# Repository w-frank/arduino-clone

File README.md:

# Battery Powered Arduino Clone

A simple battery powered Arduino clone including:
* 16 MHz ATmega328P
* I2C 2 Mbit EEPROM (24LC1025)
* I2C real-time clock/calendar (DS1337)
* UART, I2C, SPI and 7 GPIOs

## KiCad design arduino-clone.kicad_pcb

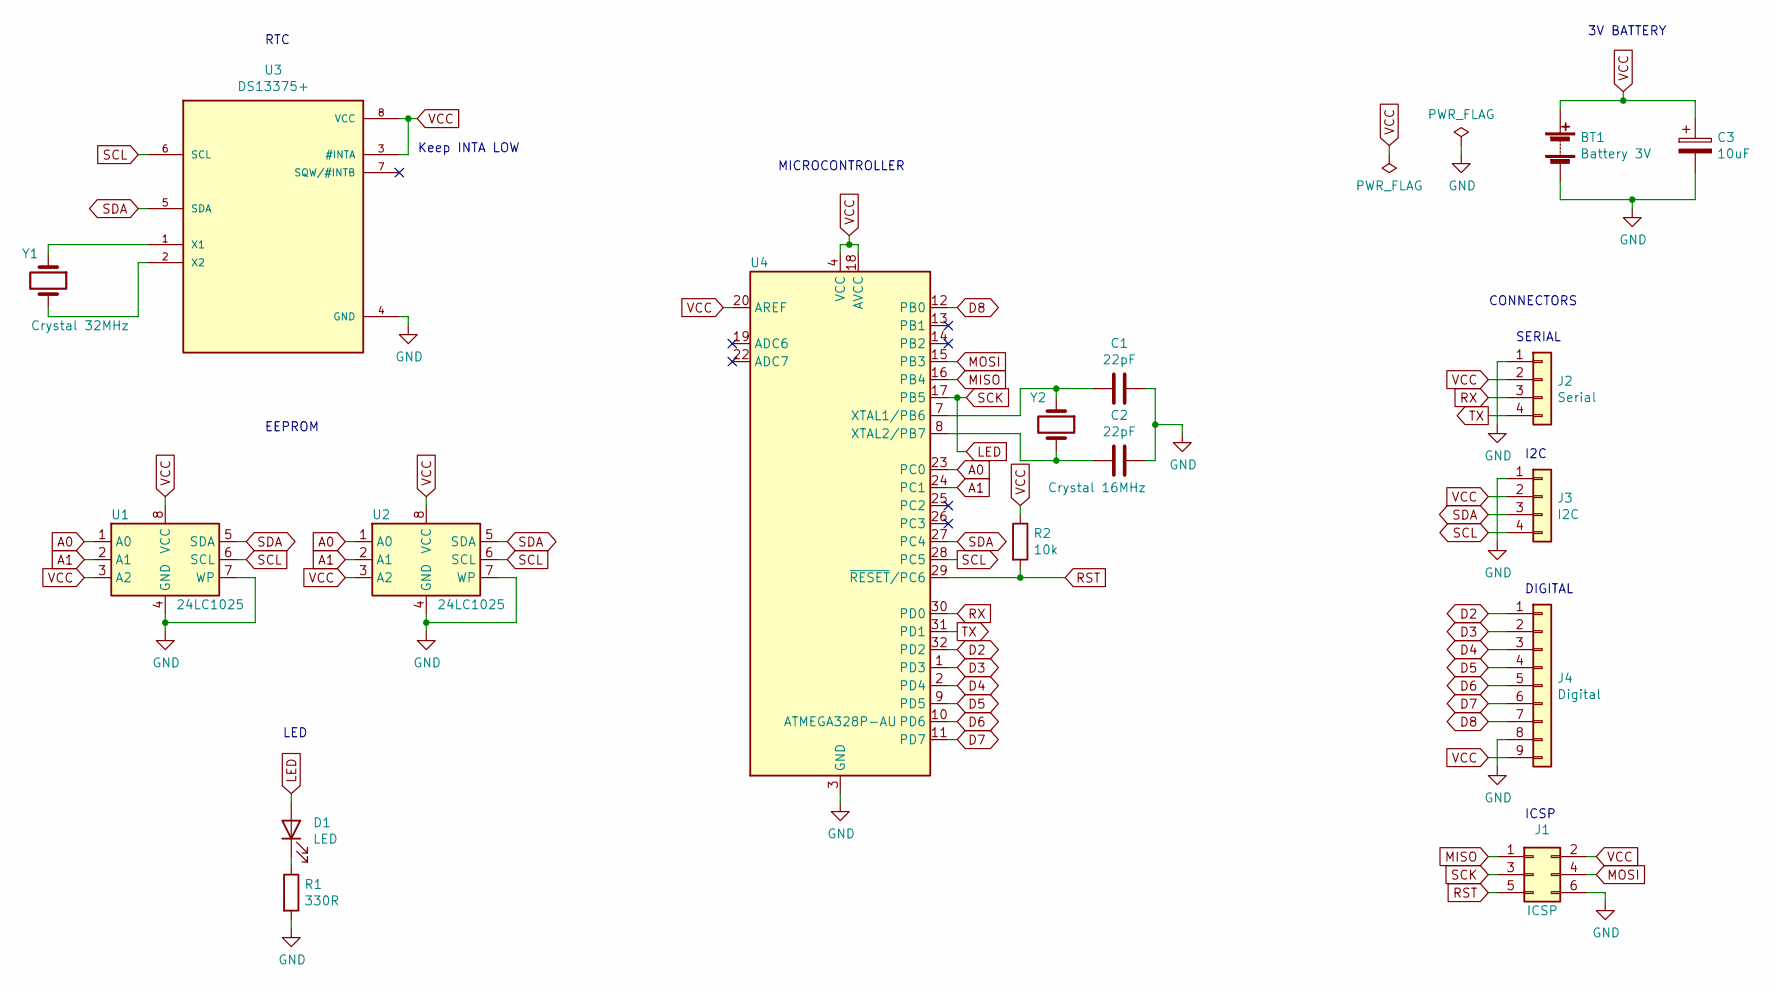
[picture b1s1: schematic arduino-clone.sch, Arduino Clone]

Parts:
BT1: Battery 3V; PinHeader_1x02_P2.54mm_Vertical
C1, C2: 22pF; C_0805_2012Metric_Pad1.15x1.40mm_HandSolder
C3: 10uF; C_0805_2012Metric_Pad1.15x1.40mm_HandSolder
D1: LED; LED_0805_2012Metric_Pad1.15x1.40mm_HandSolder
J1: ICSP; PinHeader_2x03_P2.54mm_Vertical
J2: Serial; PinSocket_1x04_P2.54mm_Vertical
J3: I2C; PinSocket_1x04_P2.54mm_Vertical
J4: Digital; PinSocket_1x09_P2.54mm_Vertical
R1: 330R; R_0805_2012Metric_Pad1.15x1.40mm_HandSolder
R2: 10k; R_0805_2012Metric_Pad1.15x1.40mm_HandSolder
U1, U2: 24LC1025; SOIJ-8_5.3x5.3mm_P1.27mm
U3: DS13375+; SO-8_5.3x6.2mm_P1.27mm
U4: ATMEGA328P-AU; TQFP-32_7x7mm_P0.8mm
Y1: Crystal 32MHz; Crystal_SMD_MicroCrystal_CC7V-T1A-2Pin_3.2x1.5mm_HandSolder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
Y2: Crystal 16MHz; Crystal_SMD_5032-2Pin_5.0x3.2mm_HandSoldering

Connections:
A0: U1.1 (A0), U2.1 (A0), U4.23 (PC0)
A1: U1.2 (A1), U2.2 (A1), U4.24 (PC1)
D2: J4.1, U4.32 (PD2)
D3: J4.2, U4.1 (PD3)
D4: J4.3, U4.2 (PD4)
D5: J4.4, U4.9 (PD5)
D6: J4.5, U4.10 (PD6)
D7: J4.6, U4.11 (PD7)
D8: J4.7, U4.12 (PB0)
GND: BT1.2 (-), C1.1, C2.1, C3.2, J1.6, J2.1, J3.1, J4.8, R1.2, U1.4 (GND), U1.7 (WP), U2.4 (GND), U2.7 (WP), U3.4 (GND), U4.3 (GND), U4.5 (GND), U4.21 (GND)
LED: D1.2 (A), J1.3, U4.17 (PB5)
MISO: J1.1, U4.16 (PB4)
MOSI: J1.4, U4.15 (PB3)
unnamed: C1.2, U4.7 (XTAL1/PB6), Y2.1
unnamed: C2.2, U4.8 (XTAL2/PB7), Y2.2
unnamed: D1.1 (K), R1.1
unnamed: U3.1 (X1), Y1.1
unnamed: U3.2 (X2), Y1.2
RST: J1.5, R2.2, U4.29 (~RESET~/PC6)
RX: J2.3, U4.30 (PD0)
SCL: J3.4, U1.6 (SCL), U2.6 (SCL), U3.6 (SCL), U4.28 (PC5)
SDA: J3.3, U1.5 (SDA), U2.5 (SDA), U3.5 (SDA), U4.27 (PC4)
TX: J2.4, U4.31 (PD1)
VCC: BT1.1 (+), C3.1, J1.2, J2.2, J3.2, J4.9, R2.1, U1.3 (A2), U1.8 (VCC), U2.3 (A2), U2.8 (VCC), U3.3 (#INTA), U3.8 (VCC), U4.4 (VCC), U4.6 (VCC), U4.18 (AVCC), U4.20 (AREF)

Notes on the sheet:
Keep INTA LOW
RTC
EEPROM
3V BATTERY
MICROCONTROLLER
LED
CONNECTORS
SERIAL
I2C
DIGITAL
ICSP

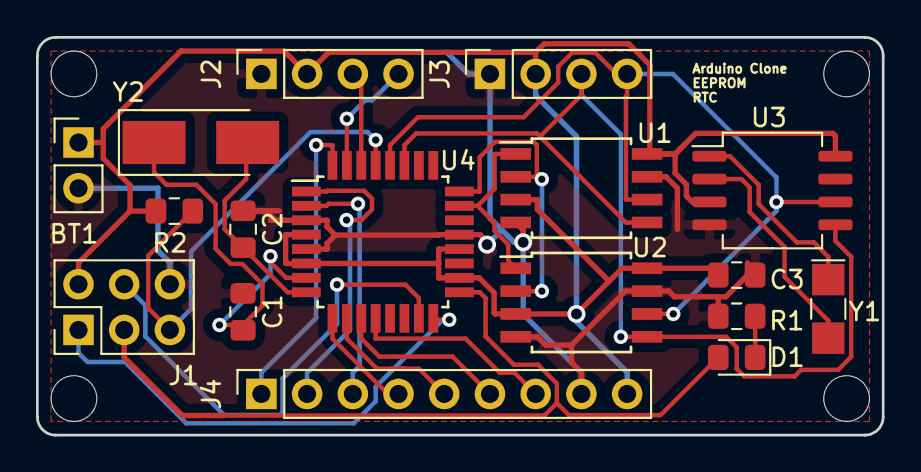
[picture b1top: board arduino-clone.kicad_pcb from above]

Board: 2 copper layers, 47.0 x 22.1 mm, 17 parts (0 on the bottom side), 24 nets.

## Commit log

2020-09-26 Include -cache.lib file and update gitignore file
2020-09-26 Add readme file
